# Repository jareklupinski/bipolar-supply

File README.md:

# bipolar-supply
Generates +-15V from a USB-C 5V Jack

The design centers around the TPS65131 chip, which integrates two switching regulators, and outputs a bipolar power supply, handy for opamps and small signal experiments.

Work in progress: tested board outputs +15 and -14V, have to recalculate inverter feedback resistors

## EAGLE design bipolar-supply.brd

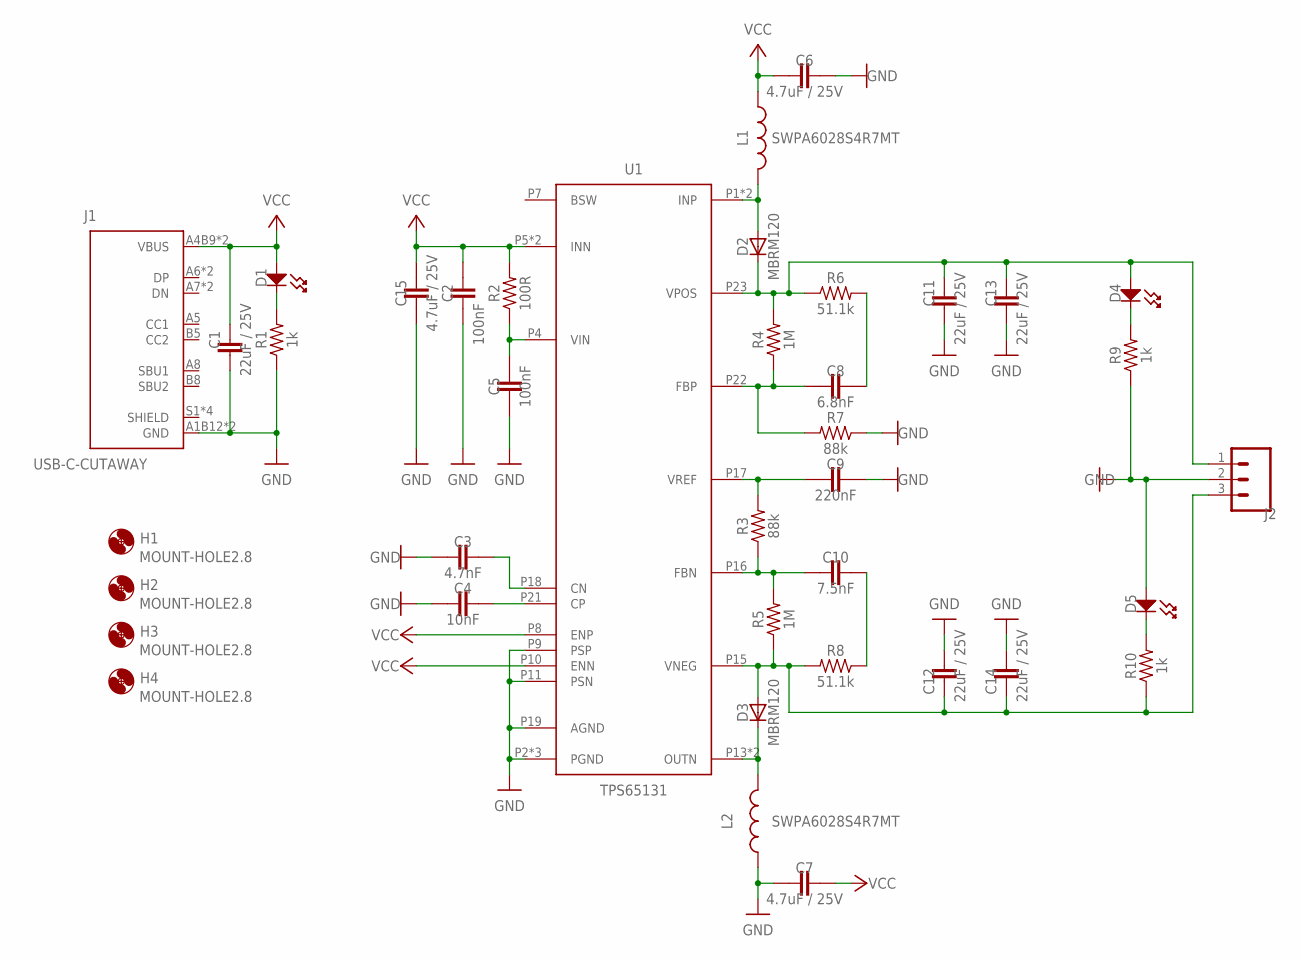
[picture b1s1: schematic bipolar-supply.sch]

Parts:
C1, C11, C12, C13, C14: 22uF / 25V; C0805
C2, C5: 100nF; C0402
C3: 4.7nF; C0402
C4: 10nF; C0402
C6, C7, C15: 4.7uF / 25V; C0402
C8: 6.8nF; C0402
C9: 220nF; C0402
C10: 7.5nF; C0402
D1, D4, D5: LED_SINGLE-0603; LED0603
D2, D3: MBRM120; POWERMITE
H1, H2, H3, H4: MOUNT-HOLE2.8; 2,8
J1: USB-C-CUTAWAY; 918-418K2024S40000
J2: CONN_03-SCREW-5MM; SCREWTERMINAL-5MM-3
L1, L2: SWPA6028S4R7MT; POWER-CHOKE_WE-TPC
R1, R9, R10: 1k; R0402
R2: 100R; R0402
R3, R7: 88k; R0402
R4, R5: 1M; R0402
R6, R8: 51.1k; R0402
U1: TPS65131; QFN24-4X4-2

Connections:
GND: C1.2, C2.1, C3.2, C4.1, C5.2, C6.1, C7.2, C9.1, C11.2, C12.2, C13.2, C14.2, C15.1, D5.ANODE, J1.A1B12 (GND), J1.B1A12 (GND), J2.2, L2.2, R1.1, R7.1, R9.1, U1.P2 (PGND), U1.P3 (PGND), U1.P9 (PSP), U1.P11 (PSN), U1.P19 (AGND), U1.PAD (PGND)
unnamed: D1.CATHODE, R1.2
unnamed: D4.CATHODE, R9.2
unnamed: D2.P$2 (A), L1.2, U1.P1 (INP), U1.P24 (INP)
unnamed: D5.CATHODE, R10.2
unnamed: C11.1, C13.1, D2.P$1 (C), D4.ANODE, J2.1, R4.2, R6.1, U1.P23 (VPOS)
unnamed: C8.2, R6.2
unnamed: C10.1, R3.1, R5.2, U1.P16 (FBN)
unnamed: C9.2, R3.2, U1.P17 (VREF)
unnamed: C8.1, R4.1, R7.2, U1.P22 (FBP)
unnamed: C10.2, R8.1
unnamed: C12.1, C14.1, D3.P$2 (A), J2.3, R5.1, R8.2, R10.1, U1.P15 (VNEG)
unnamed: C4.2, U1.P21 (CP)
unnamed: C3.1, U1.P18 (CN)
unnamed: C5.1, R2.1, U1.P4 (VIN)
unnamed: D3.P$1 (C), L2.1, U1.P13 (OUTN), U1.P14 (OUTN)
VCC: C1.1, C2.2, C6.2, C7.1, C15.2, D1.ANODE, J1.A4B9 (VBUS), J1.B4A9 (VBUS), L1.1, R2.2, U1.P5 (INN), U1.P6 (INN), U1.P8 (ENP), U1.P10 (ENN)

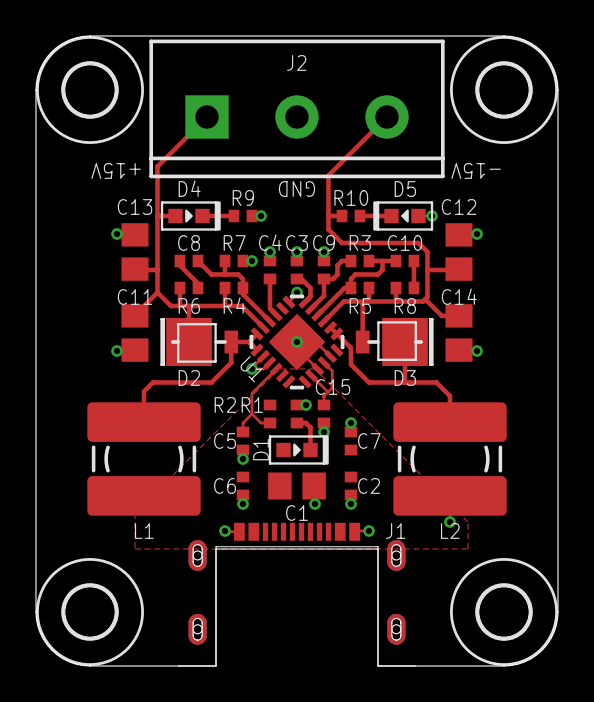
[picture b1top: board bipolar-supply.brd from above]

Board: 2 copper layers, 29.0 x 35.0 mm, 39 parts (0 on the bottom side), 17 nets.

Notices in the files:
parts and their libraries:
SparkFun-Connectors: Licensing: Creative Commons ShareAlike 4.0 International - https://creativecommons.org/licenses/by-sa/4.0
